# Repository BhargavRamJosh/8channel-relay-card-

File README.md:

#  8 Channel Relay Module

## 🔌 Project Overview
This project demonstrates the design of an **8 Channel Relay Driver Board** capable of controlling **multiple AC/DC loads** through microcontrollers like **Arduino, ESP32, or Raspberry Pi**.  
Each relay can be triggered individually, allowing automation of lights, fans, and other appliances.

---

## 📷 Project Images

| PCB Layout | Schematic | 3D View |
|-------------|------------|---------|
|  |  |  |

---

## ⚙ Circuit Working

| Stage | Component | Function |
|--------|------------|-----------|
| **Input Control** | Signal Pins (IN1–IN8) | Control each relay channel via Arduino or ESP32 |
| **Relay Driver** | Transistors / ULN2803 | Acts as a switching driver between microcontroller and relay |
| **Relays** | 8× SPDT (5V or 12V) | Switch AC/DC loads up to 10A |
| **Indicator LEDs** | 8 LEDs | Indicate active relay channels |
| **Power Section** | JD-VCC, VCC, GND Pins | Provides isolated power for relay coils and logic |

---

## ✅ Features

- **8 independent relay channels**
- **Optocoupler / transistor isolation** for safety
- **LED indicators** for each channel
- **Screw terminal outputs** for easy load connection
- Compatible with **Arduino, ESP32, Raspberry Pi, and STM32**

---

## 🧾 Components List

| Component | Specification | Quantity |
|-----------|----------------|-----------|
| Relays | SPDT, 5V or 12V, 10A | 8 |
| Transistor / Driver IC | ULN2803 / BC547 | 8 / 1 |
| Resistors | 1kΩ–10kΩ | As required |
| Indicator LEDs | Red | 8 |
| Screw Terminals | 2-Pin / 3-Pin | 8 |
| Input Header | 10-Pin Male Header | 1 |
| Power Supply Pins | JD-VCC, VCC, GND | 1 set |

---

## ⚡ Applications

- **Home automation systems**
- **Industrial control**
- **Smart IoT devices**
- **Multiple appliance switching**
- **Arduino and ESP32 projects**

---

## 🧑‍💻 Author

**Bhargav Ram**  
Electronics and Communication Engineering Student  
Passionate about **Embedded Systems | IoT | PCB Design**

---

⭐ *If you like this project, give it a star on GitHub and share your feedback!*

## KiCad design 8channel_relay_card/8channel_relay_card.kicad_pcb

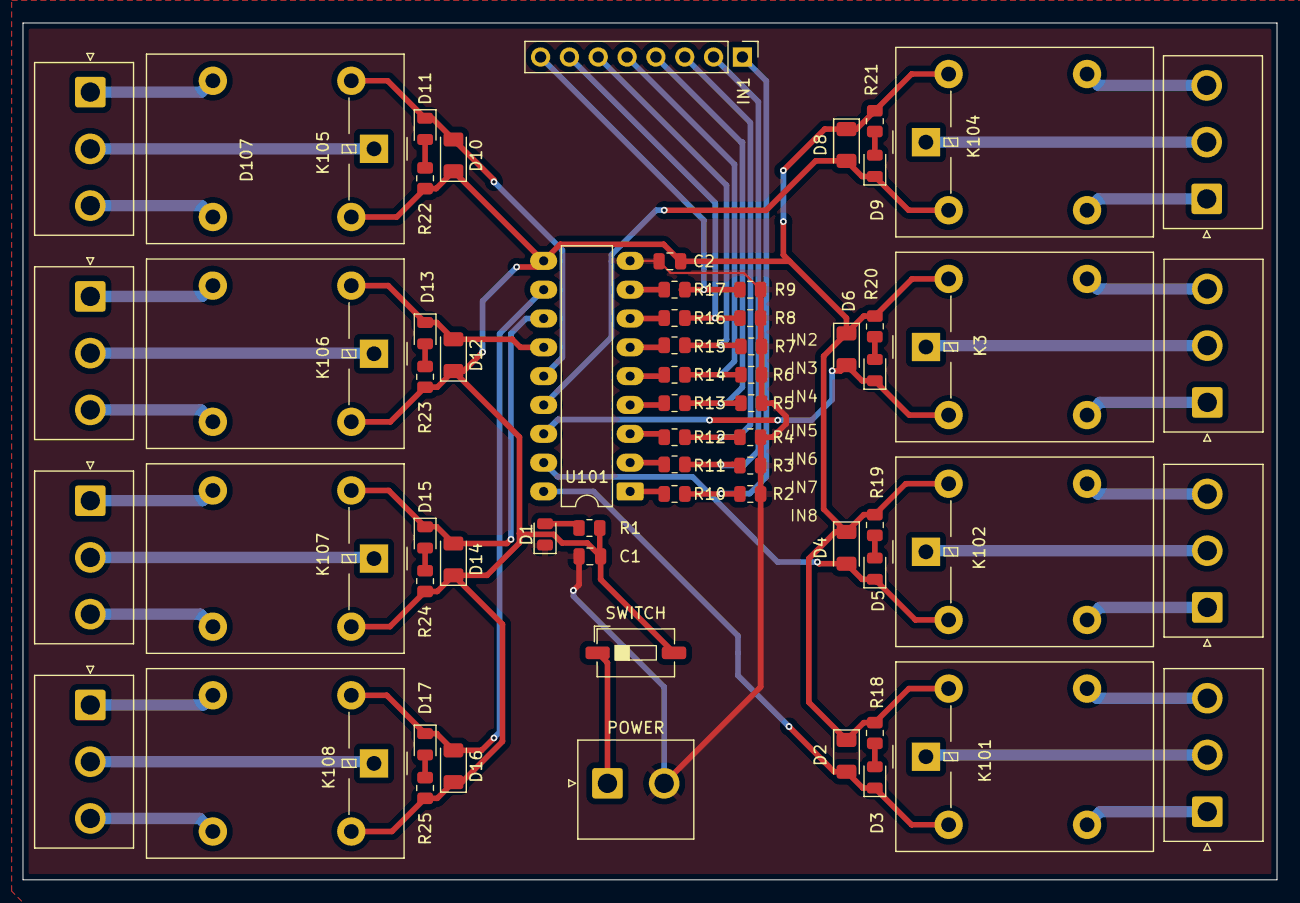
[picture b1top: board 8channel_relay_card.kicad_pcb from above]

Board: 2 copper layers, 110.5 x 75.5 mm, 64 parts (0 on the bottom side), 60 nets.

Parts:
C1, C2: 100nF; C_0805_2012Metric
D1, D3, D5, D9, D11, D13, D15, D17, D107: LED; LED_0805_2012Metric
D2, D4, D6, D8, D10, D12, D14, D16: D_Small; D_1206_3216Metric
IN1: INPUT; PinHeader_1x08_P2.54mm_Vertical
J103, J104, J105, J106, J107, J108, J109, J110: NC CO NO; JST_NV_B03P-NV_1x03_P5.00mm_Vertical
K3, K101, K102, K104, K105, K106, K107, K108: G5LE-1; Relay_SPDT_Omron-G5LE-1
POWER: POWER; JST_NV_B02P-NV_1x02_P5.00mm_Vertical
R1, R18, R19, R20, R21, R22, R23, R24, R25: 680E; R_0805_2012Metric
R2, R3, R4, R5, R6, R7, R8, R9, R10, R11, R12, R13, R14, R15, R16, R17: 10K; R_0805_2012Metric
SWITCH: SW_SPST; SW_DIP_SPSTx01_Slide_6.7x4.1mm_W6.73mm_P2.54mm_LowProfile_J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
U101: ULN2803A; DIP-18_W7.62mm_LongPads

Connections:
/O1: D2.2 (A), D3.1 (K), K101.2, U101.18 (O1)
/O2: D4.2 (A), D5.1 (K), K102.2, U101.17 (O2)
/O3: D6.2 (A), D107.1 (K), K3.2, U101.16 (O3)
/O4: D8.2 (A), D9.1 (K), K104.2, U101.15 (O4)
/O5: D10.2 (A), D11.1 (K), K105.2, U101.14 (O5)
/O6: D12.2 (A), D13.1 (K), K106.2, U101.13 (O6)
/O7: D14.2 (A), D15.1 (K), K107.2, U101.12 (O7)
/O8: D16.2 (A), D17.1 (K), K108.2, U101.11 (O8)
GND: C1.2, C2.2, D1.1 (K), POWER.2, R2.2, R3.2, R4.2, R5.2, R6.2, R7.2, R8.2, R9.2, U101.9 (GND)
unnamed: D1.2 (A), R1.2
unnamed: D3.2 (A), R18.2
unnamed: D5.2 (A), R19.2
unnamed: D107.2 (A), R20.2
unnamed: D9.2 (A), R21.2
unnamed: D11.2 (A), R22.2
unnamed: D13.2 (A), R23.2
unnamed: D15.2 (A), R24.2
unnamed: D17.2 (A), R25.2
unnamed: POWER.1, SWITCH.1 (A)
unnamed: IN1.1, R2.1, R10.1
unnamed: IN1.2, R3.1, R11.1
unnamed: IN1.3, R4.1, R12.1
unnamed: IN1.4, R5.1, R13.1
unnamed: IN1.5, R6.1, R14.1
unnamed: IN1.6, R7.1, R15.1
unnamed: IN1.7, R8.1, R16.1
unnamed: IN1.8, R9.1, R17.1
unnamed: J103.1, K101.3
unnamed: J103.2, K101.1
unnamed: J103.3, K101.4
unnamed: J104.1, K102.3
unnamed: J104.2, K102.1
unnamed: J104.3, K102.4
unnamed: J105.1, K3.3
unnamed: J105.2, K3.1
unnamed: J105.3, K3.4
unnamed: J106.1, K104.3
unnamed: J106.2, K104.1
unnamed: J106.3, K104.4
unnamed: J107.1, K105.3
unnamed: J107.2, K105.1
unnamed: J107.3, K105.4
unnamed: J108.1, K106.3
unnamed: J108.2, K106.1
unnamed: J108.3, K106.4
unnamed: J109.1, K107.3
unnamed: J109.2, K107.1
unnamed: J109.3, K107.4
unnamed: J110.1, K108.3
unnamed: J110.2, K108.1
unnamed: J110.3, K108.4
unnamed: R10.2, U101.1 (I1)
unnamed: R11.2, U101.2 (I2)
unnamed: R12.2, U101.3 (I3)
unnamed: R13.2, U101.4 (I4)
unnamed: R14.2, U101.5 (I5)
unnamed: R15.2, U101.6 (I6)
unnamed: R16.2, U101.7 (I7)
unnamed: R17.2, U101.8 (I8)
VCC: C1.1, C2.1, D2.1 (K), D4.1 (K), D6.1 (K), D8.1 (K), D10.1 (K), D12.1 (K), D14.1 (K), D16.1 (K), K3.5, K101.5, K102.5, K104.5, K105.5, K106.5, K107.5, K108.5, R1.1, R18.1, R19.1, R20.1, R21.1, R22.1, R23.1, R24.1, R25.1, SWITCH.2 (B), U101.10 (COM)
